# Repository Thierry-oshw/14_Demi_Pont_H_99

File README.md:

# 13_TOR_N
 Tout Ou Rien à la masse

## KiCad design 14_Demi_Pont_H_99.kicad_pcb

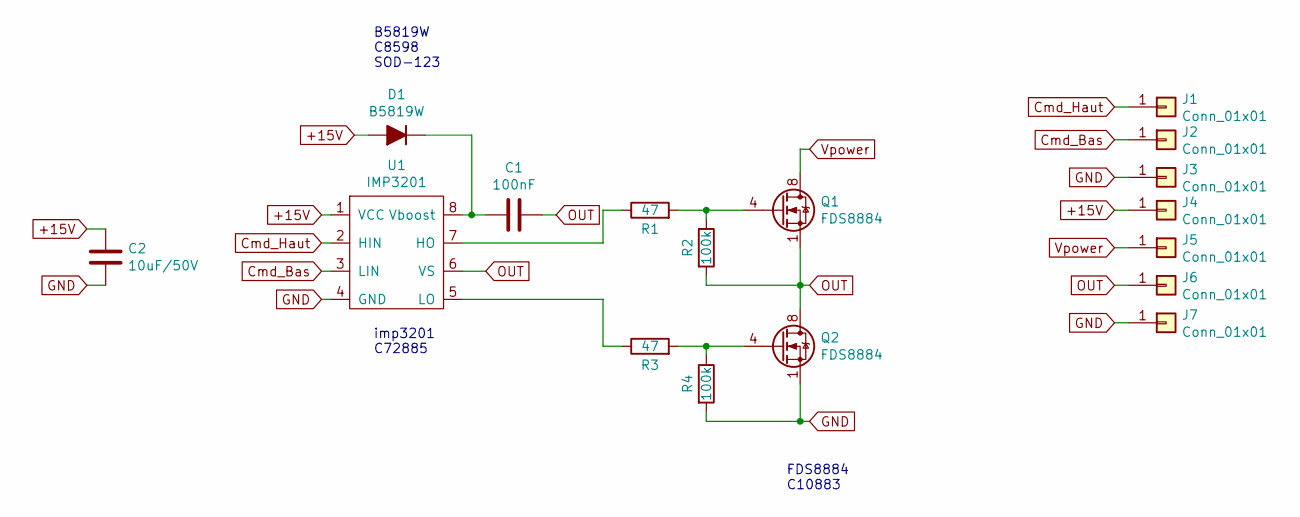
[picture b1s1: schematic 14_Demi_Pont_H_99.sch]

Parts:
C1: 100nF; C_0603_1608Metric
C2: 10uF/50V; C_1210_3225Metric
D1: B5819W; D_SOD-123
J1, J2, J3, J4, J5, J6, J7: Conn_01x01; Castellated_conn
Q1, Q2: FDS8884; SOIC-8_3.9x4.9mm_P1.27mm
R1, R3: 47; R_0603_1608Metric_Pad1.05x0.95mm_HandSolder
R2, R4: 100k; R_0603_1608Metric_Pad1.05x0.95mm_HandSolder
U1: IMP3201; SOP-8_3.9x4.9mm_P1.27mm

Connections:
+15V: C2.1, D1.2 (A), J4.1, U1.1 (VCC)
Cmd_Bas: J2.1, U1.3 (LIN)
Cmd_Haut: J1.1, U1.2 (HIN)
GND: C2.2, J3.1, J7.1, Q2.1 (S), Q2.2 (S), Q2.3 (S), R4.2, U1.4 (GND)
unnamed: C1.2, D1.1 (K), U1.8 (Vboost)
unnamed: Q1.4 (G), R1.2, R2.1
unnamed: Q2.4 (G), R3.2, R4.1
unnamed: R1.1, U1.7 (HO)
unnamed: R3.1, U1.5 (LO)
OUT: C1.1, J6.1, Q1.1 (S), Q1.2 (S), Q1.3 (S), Q2.5 (D), Q2.6 (D), Q2.7 (D), Q2.8 (D), R2.2, U1.6 (VS)
Vpower: J5.1, Q1.5 (D), Q1.6 (D), Q1.7 (D), Q1.8 (D)

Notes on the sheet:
FDS8884 C10883
imp3201 C72885
B5819W C8598 SOD-123

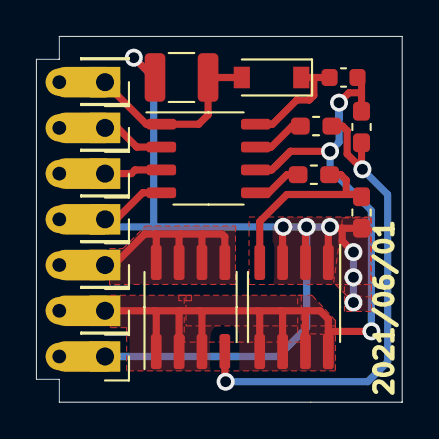
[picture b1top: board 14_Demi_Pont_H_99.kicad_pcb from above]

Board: 2 copper layers, 20.3 x 20.3 mm, 17 parts (0 on the bottom side), 11 nets.

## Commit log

2021-06-01 schema + routage
2021-07-26 maj split libraires
2023-05-02 chgt nom fichier licence
